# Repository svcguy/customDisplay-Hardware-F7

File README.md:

A custom display development PCB targeted to be compatible with STM32CubeMX and TouchGFX.  
Based on the STM32F767 MCU with 128Mbit external SDRAM, 512Mbit external QSPI flash.
PCB is designed to be compatible with JLCPCB's SMT service.

More to come!
Work in progress!

Changelog:
Rev A0 -    inital design.  Sent to fab
Rev B1 -    PCB changes -       move traces too close to PCB edge
                                change C23 footprint to 0805 (bom consolidation)
                                move some dimensions to B.Fab layer
            Schematic changes - change C23 footprint to 0805 (bom consolidation)
                                update some footprint properties to "virtual"
            General changes -   Generate PDF of schematic and top and bot assembly drawings

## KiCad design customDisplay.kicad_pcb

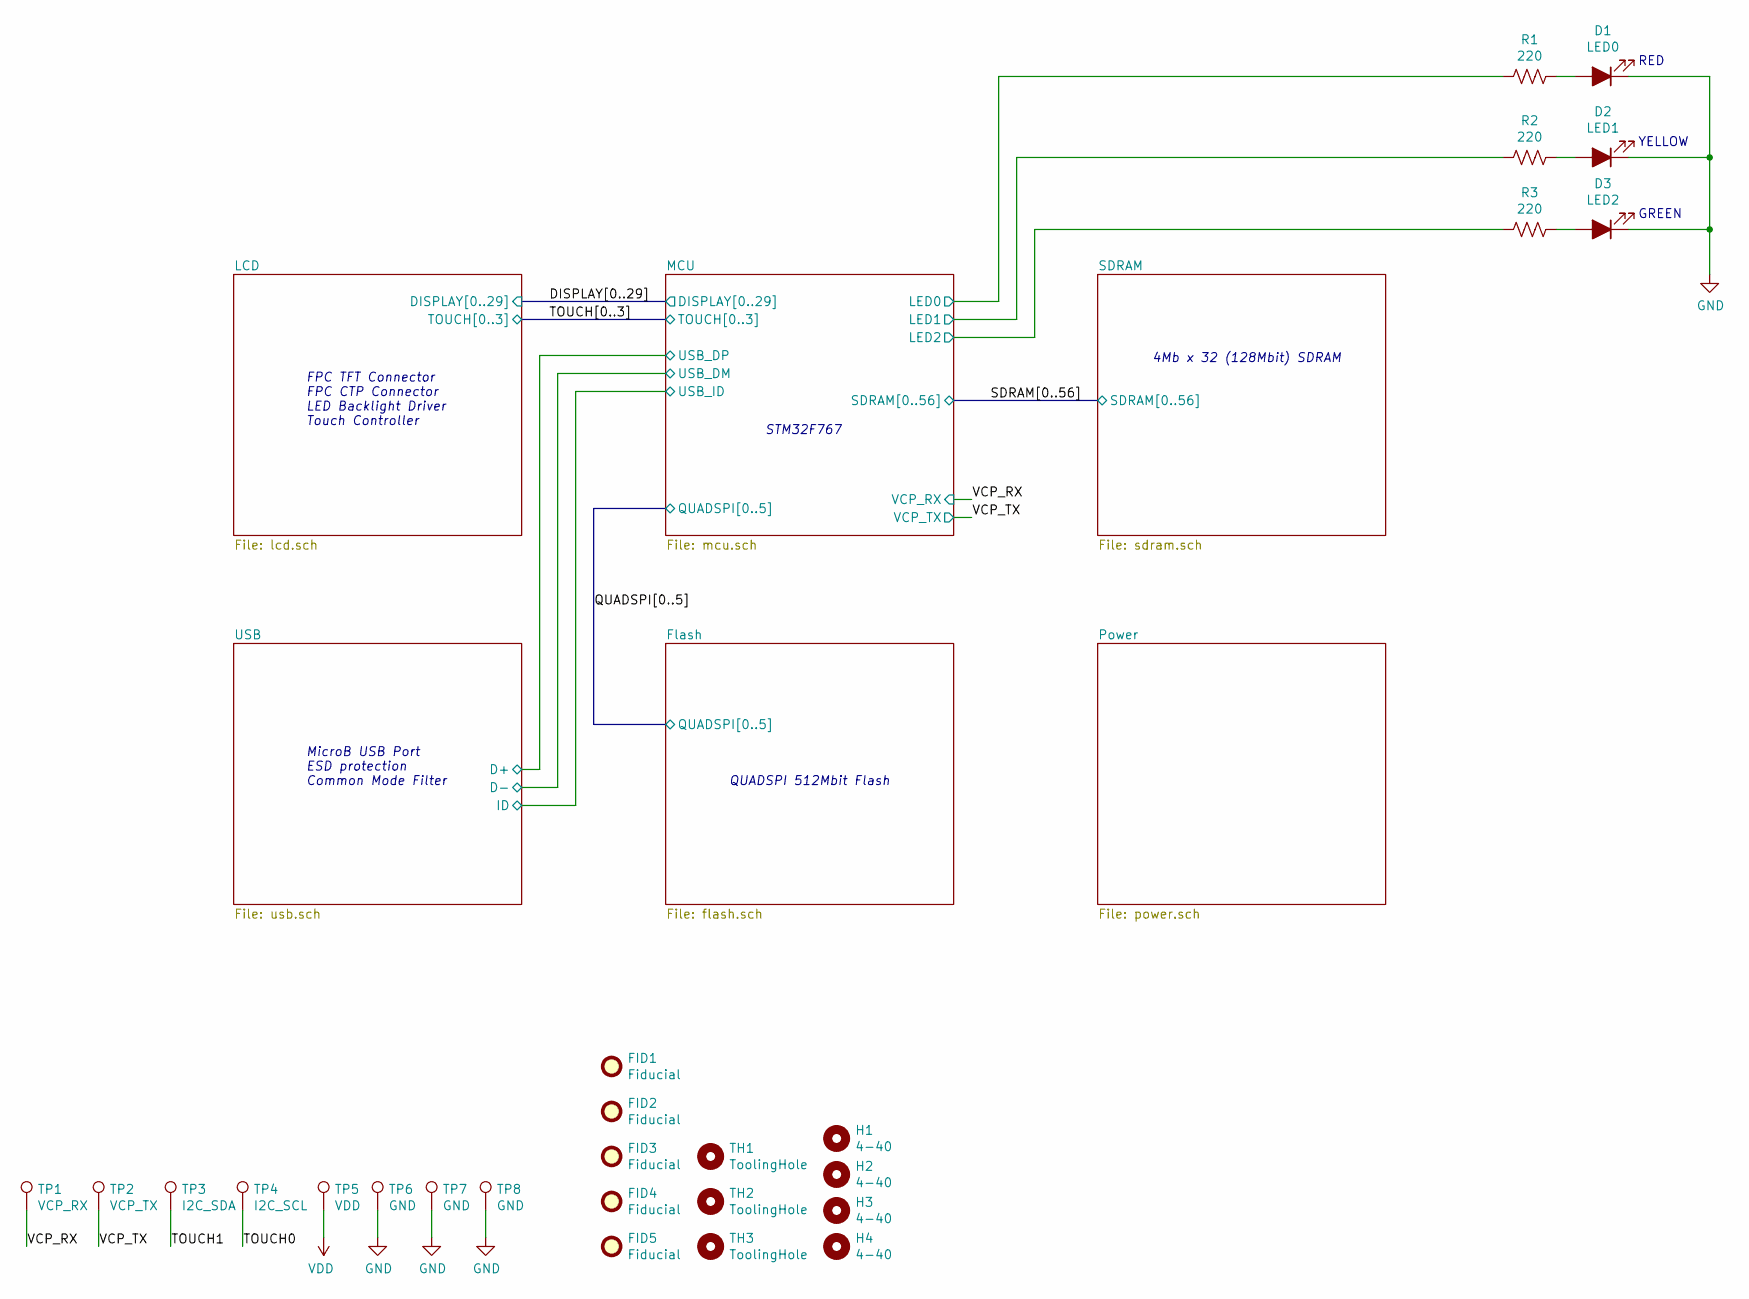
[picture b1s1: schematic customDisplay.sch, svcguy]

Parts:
D1: LED0; LED_0603_1608Metric; LCSC C2286
D2: LED1; LED_0603_1608Metric; LCSC C72038
D3: LED2; LED_0603_1608Metric; LCSC C72043
FID1, FID2, FID3, FID4, FID5: Fiducial; Fiducial_1mm_Mask2mm; Digikey DNP
H1, H2, H3, H4: 4-40; MountingHole_3.2mm_M3; LCSC DNP
R1, R2, R3: 220; R_0402_1005Metric; LCSC C25091
TH1, TH2, TH3: ToolingHole; JLC_TOOLING_HOLE; Digikey DNP
TP1: VCP_RX; TestPoint_THTPad_1.0x1.0mm_Drill0.5mm; LCSC DNP
TP2: VCP_TX; TestPoint_THTPad_1.0x1.0mm_Drill0.5mm; LCSC DNP
TP3: I2C_SDA; TestPoint_THTPad_1.0x1.0mm_Drill0.5mm; LCSC DNP
TP4: I2C_SCL; TestPoint_THTPad_1.0x1.0mm_Drill0.5mm; LCSC DNP
TP5: VDD; TestPoint_THTPad_1.0x1.0mm_Drill0.5mm; LCSC DNP
TP6, TP7: GND; TestPoint_THTPad_1.0x1.0mm_Drill0.5mm; LCSC DNP
TP8: GND; H9001-01; LCSC DNP

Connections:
/MCU/LED0: R1.2; also elsewhere on the board
/MCU/LED1: R2.2; also elsewhere on the board
/MCU/LED2: R3.2; also elsewhere on the board
/TOUCH0: TP4.1; also elsewhere on the board
/TOUCH1: TP3.1; also elsewhere on the board
/VCP_RX: TP1.1; also elsewhere on the board
/VCP_TX: TP2.1; also elsewhere on the board
GND: D1.1 (K), D2.1 (K), D3.1 (K), TP6.1, TP7.1, TP8.1; also elsewhere on the board
unnamed: D1.2 (A), R1.1
unnamed: D2.2 (A), R2.1
unnamed: D3.2 (A), R3.1
VDD: TP5.1; also elsewhere on the board

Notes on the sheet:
RED
YELLOW
GREEN
FPC TFT Connector FPC CTP Connector LED Backlight Driver Touch Controller
MicroB USB Port ESD protection Common Mode Filter
QUADSPI 512Mbit Flash
4Mb x 32 (128Mbit) SDRAM
STM32F767

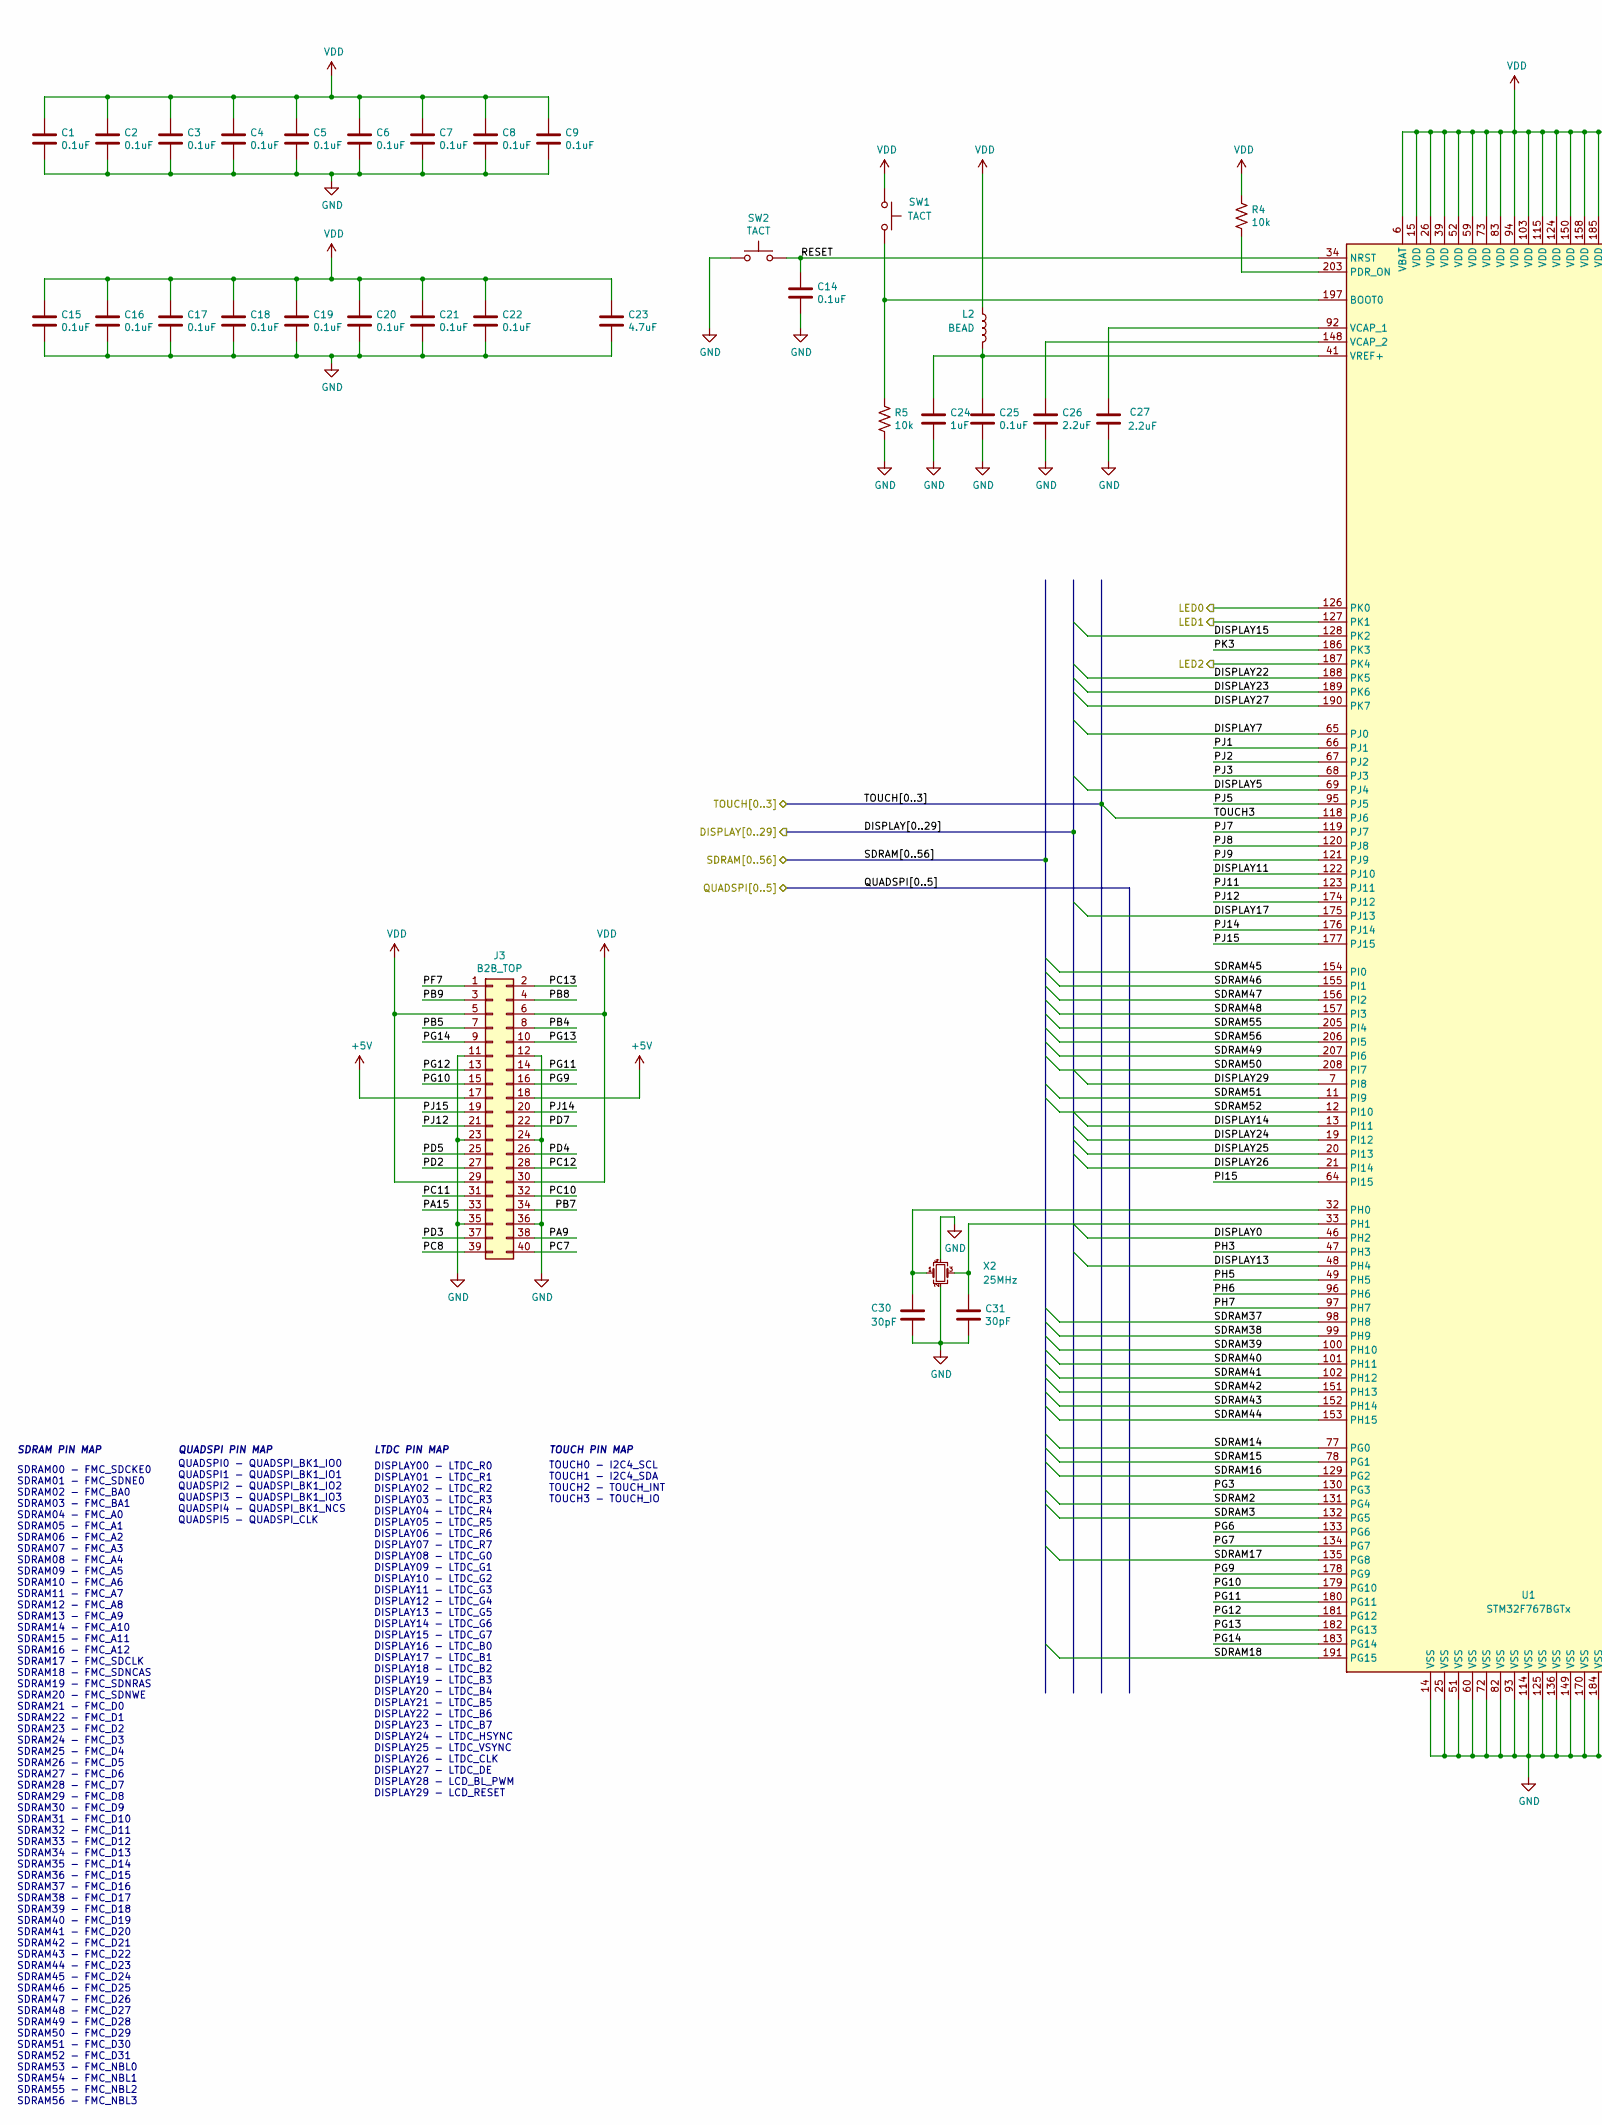
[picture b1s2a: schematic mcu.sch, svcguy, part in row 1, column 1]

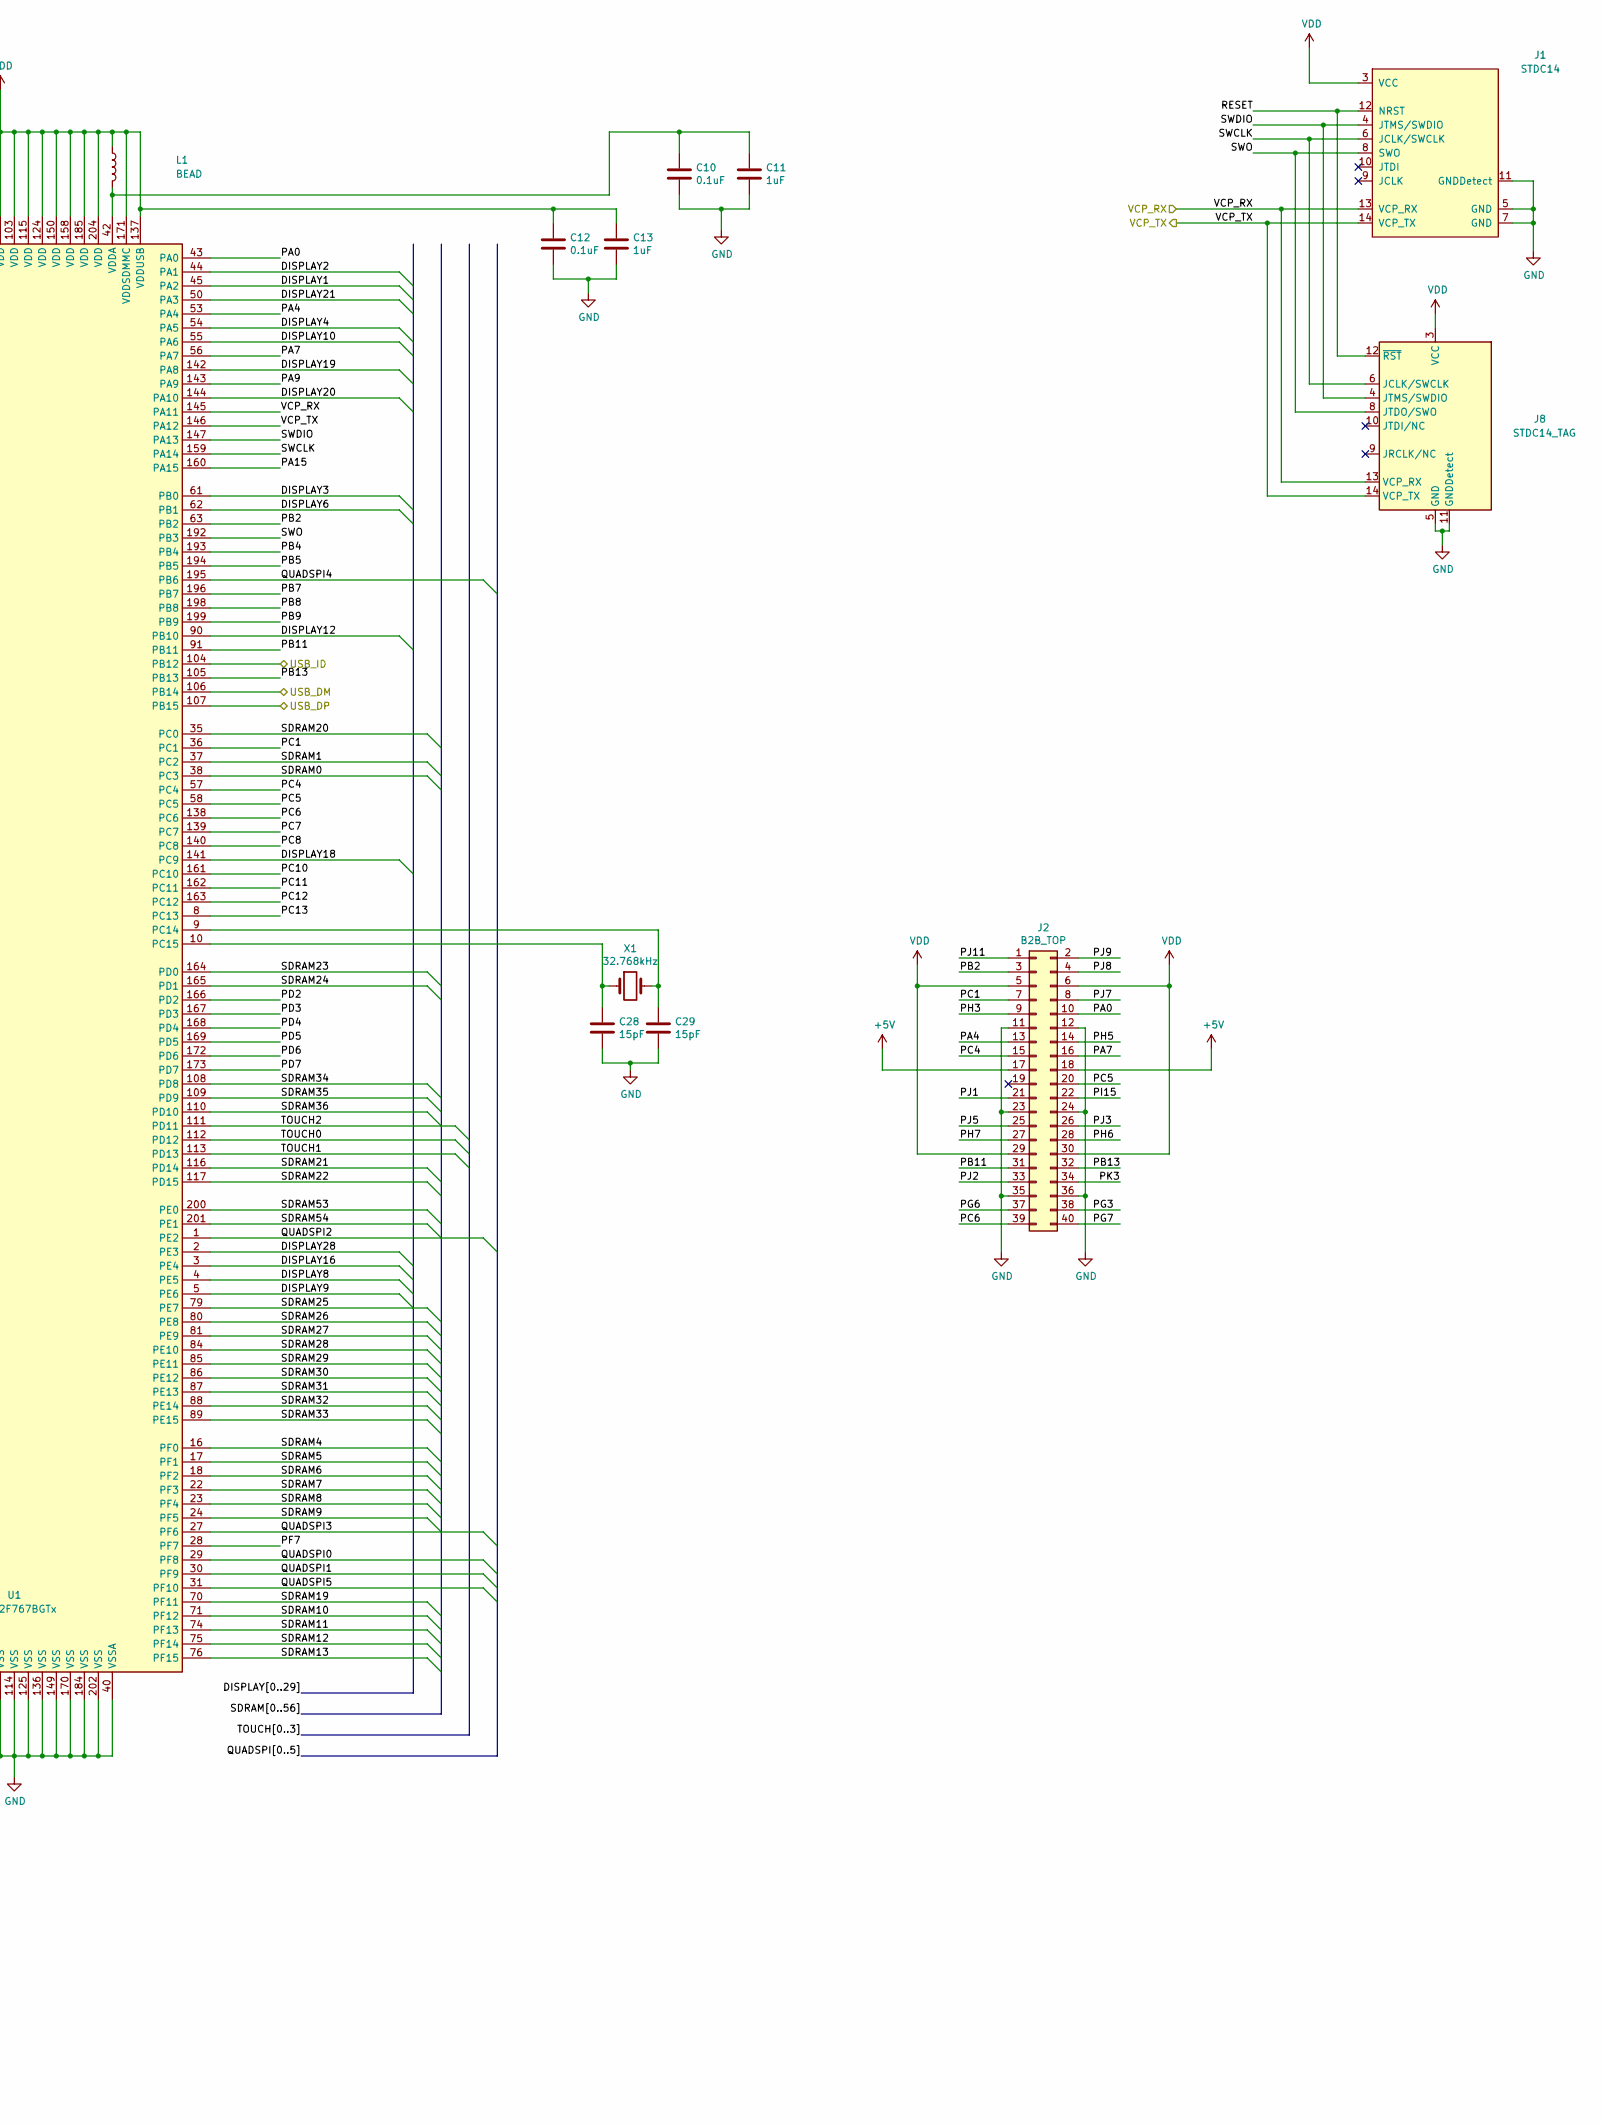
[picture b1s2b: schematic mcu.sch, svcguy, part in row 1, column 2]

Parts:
C1, C2, C3, C4, C5, C6, C7, C8, C9, C10, C12, C14, C15, C16, C17, C18, C19, C20, C21, C22, C25: 0.1uF; C_0402_1005Metric; LCSC C1525
C11, C13, C24: 1uF; C_0402_1005Metric; LCSC C52923
C23: 4.7uF; C_0805_2012Metric; LCSC C19666
C26, C27: 2.2uF; C_0603_1608Metric; LCSC C23630
C28, C29: 15pF; C_0402_1005Metric; LCSC C1548
C30, C31: 30pF; C_0402_1005Metric; LCSC C1570
J1: STDC14; STDC14_BOX; LCSC DNP
J2, J3: B2B_TOP; FX6A-040P-0.8SV; LCSC DNP
J8: STDC14_TAG; Tag-Connect_TC2070-IDC-FP_2x07_P1.27mm_Vertical; LCSC DNP
L1, L2: BEAD; L_0805_2012Metric; LCSC C1015
R4, R5: 10k; R_0402_1005Metric; LCSC C25744
SW1, SW2: TACT; TS_1187A; LCSC C318889
U1: STM32F767BGTx; LQFP-208_28x28mm_P0.5mm; LCSC C129277
X1: 32.768kHz; Crystal_SMD_3215-2Pin_3.2x1.5mm; LCSC C32346
X2: 25MHz; Crystal_SMD_3225-4Pin_3.2x2.5mm; LCSC C9006

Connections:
+5V: J2.17, J2.18, J3.17, J3.18; also elsewhere on the board
/Flash/QUADSPI0: U1.29 (PF8); also elsewhere on the board
/Flash/QUADSPI1: U1.30 (PF9); also elsewhere on the board
/Flash/QUADSPI2: U1.1 (PE2); also elsewhere on the board
/Flash/QUADSPI3: U1.27 (PF6); also elsewhere on the board
/Flash/QUADSPI4: U1.195 (PB6); also elsewhere on the board
/Flash/QUADSPI5: U1.31 (PF10); also elsewhere on the board
/LCD/DISPLAY0: U1.46 (PH2); also elsewhere on the board
/LCD/DISPLAY1: U1.45 (PA2); also elsewhere on the board
/LCD/DISPLAY2: U1.44 (PA1); also elsewhere on the board
/LCD/DISPLAY3: U1.61 (PB0); also elsewhere on the board
/LCD/DISPLAY4: U1.54 (PA5); also elsewhere on the board
/LCD/DISPLAY5: U1.69 (PJ4); also elsewhere on the board
/LCD/DISPLAY6: U1.62 (PB1); also elsewhere on the board
/LCD/DISPLAY7: U1.65 (PJ0); also elsewhere on the board
/LCD/DISPLAY8: U1.4 (PE5); also elsewhere on the board
/LCD/DISPLAY9: U1.5 (PE6); also elsewhere on the board
/LCD/DISPLAY10: U1.55 (PA6); also elsewhere on the board
/LCD/DISPLAY11: U1.122 (PJ10); also elsewhere on the board
/LCD/DISPLAY12: U1.90 (PB10); also elsewhere on the board
/LCD/DISPLAY13: U1.48 (PH4); also elsewhere on the board
/LCD/DISPLAY14: U1.13 (PI11); also elsewhere on the board
/LCD/DISPLAY15: U1.128 (PK2); also elsewhere on the board
/LCD/DISPLAY16: U1.3 (PE4); also elsewhere on the board
/LCD/DISPLAY17: U1.175 (PJ13); also elsewhere on the board
/LCD/DISPLAY18: U1.141 (PC9); also elsewhere on the board
/LCD/DISPLAY19: U1.142 (PA8); also elsewhere on the board
/LCD/DISPLAY20: U1.144 (PA10); also elsewhere on the board
/LCD/DISPLAY21: U1.50 (PA3); also elsewhere on the board
/LCD/DISPLAY22: U1.188 (PK5); also elsewhere on the board
/LCD/DISPLAY23: U1.189 (PK6); also elsewhere on the board
/LCD/DISPLAY24: U1.19 (PI12); also elsewhere on the board
/LCD/DISPLAY25: U1.20 (PI13); also elsewhere on the board
/LCD/DISPLAY26: U1.21 (PI14); also elsewhere on the board
/LCD/DISPLAY27: U1.190 (PK7); also elsewhere on the board
/LCD/DISPLAY28: U1.2 (PE3); also elsewhere on the board
/LCD/DISPLAY29: U1.7 (PI8); also elsewhere on the board
/LCD/TOUCH2: U1.111 (PD11); also elsewhere on the board
/LCD/TOUCH3: U1.118 (PJ6); also elsewhere on the board
/MCU/LED0: U1.126 (PK0); also elsewhere on the board
/MCU/LED1: U1.127 (PK1); also elsewhere on the board
/MCU/LED2: U1.187 (PK4); also elsewhere on the board
/MCU/PA0: J2.10, U1.43 (PA0)
/MCU/PA4: J2.13, U1.53 (PA4)
/MCU/PA7: J2.16, U1.56 (PA7)
/MCU/PA9: J3.38, U1.143 (PA9)
/MCU/PA15: J3.33, U1.160 (PA15)
/MCU/PB2: J2.3, U1.63 (PB2)
/MCU/PB4: J3.8, U1.193 (PB4)
/MCU/PB5: J3.7, U1.194 (PB5)
/MCU/PB7: J3.34, U1.196 (PB7)
/MCU/PB8: J3.4, U1.198 (PB8)
/MCU/PB9: J3.3, U1.199 (PB9)
/MCU/PB11: J2.31, U1.91 (PB11)
/MCU/PB13: J2.32, U1.105 (PB13)
/MCU/PC1: J2.7, U1.36 (PC1)
/MCU/PC4: J2.15, U1.57 (PC4)
/MCU/PC5: J2.20, U1.58 (PC5)
/MCU/PC6: J2.39, U1.138 (PC6)
/MCU/PC7: J3.40, U1.139 (PC7)
/MCU/PC8: J3.39, U1.140 (PC8)
/MCU/PC10: J3.32, U1.161 (PC10)
/MCU/PC11: J3.31, U1.162 (PC11)
/MCU/PC12: J3.28, U1.163 (PC12)
/MCU/PC13: J3.2, U1.8 (PC13)
/MCU/PD2: J3.27, U1.166 (PD2)
/MCU/PD3: J3.37, U1.167 (PD3)
/MCU/PD4: J3.26, U1.168 (PD4)
/MCU/PD5: J3.25, U1.169 (PD5)
/MCU/PD7: J3.22, U1.173 (PD7)
/MCU/PF7: J3.1, U1.28 (PF7)
/MCU/PG3: J2.38, U1.130 (PG3)
/MCU/PG6: J2.37, U1.133 (PG6)
/MCU/PG7: J2.40, U1.134 (PG7)
/MCU/PG9: J3.16, U1.178 (PG9)
/MCU/PG10: J3.15, U1.179 (PG10)
/MCU/PG11: J3.14, U1.180 (PG11)
/MCU/PG12: J3.13, U1.181 (PG12)
/MCU/PG13: J3.10, U1.182 (PG13)
/MCU/PG14: J3.9, U1.183 (PG14)
/MCU/PH3: J2.9, U1.47 (PH3)
/MCU/PH5: J2.14, U1.49 (PH5)
/MCU/PH6: J2.28, U1.96 (PH6)
/MCU/PH7: J2.27, U1.97 (PH7)
/MCU/PI15: J2.22, U1.64 (PI15)
/MCU/PJ1: J2.21, U1.66 (PJ1)
/MCU/PJ2: J2.33, U1.67 (PJ2)
/MCU/PJ3: J2.26, U1.68 (PJ3)
/MCU/PJ5: J2.25, U1.95 (PJ5)
/MCU/PJ7: J2.8, U1.119 (PJ7)
/MCU/PJ8: J2.4, U1.120 (PJ8)
/MCU/PJ9: J2.2, U1.121 (PJ9)
/MCU/PJ11: J2.1, U1.123 (PJ11)
/MCU/PJ12: J3.21, U1.174 (PJ12)
/MCU/PJ14: J3.20, U1.176 (PJ14)
/MCU/PJ15: J3.19, U1.177 (PJ15)
/MCU/PK3: J2.34, U1.186 (PK3)
/MCU/RESET: C14.1, J1.12 (NRST), J8.12 (~RST), SW2.2, U1.34 (NRST)
/MCU/SDRAM0: U1.38 (PC3); also elsewhere on the board
/MCU/SDRAM1: U1.37 (PC2); also elsewhere on the board
/MCU/SDRAM2: U1.131 (PG4); also elsewhere on the board
/MCU/SDRAM3: U1.132 (PG5); also elsewhere on the board
/MCU/SDRAM4: U1.16 (PF0); also elsewhere on the board
/MCU/SDRAM5: U1.17 (PF1); also elsewhere on the board
/MCU/SDRAM6: U1.18 (PF2); also elsewhere on the board
/MCU/SDRAM7: U1.22 (PF3); also elsewhere on the board
/MCU/SDRAM8: U1.23 (PF4); also elsewhere on the board
/MCU/SDRAM9: U1.24 (PF5); also elsewhere on the board
/MCU/SDRAM10: U1.71 (PF12); also elsewhere on the board
/MCU/SDRAM11: U1.74 (PF13); also elsewhere on the board
/MCU/SDRAM12: U1.75 (PF14); also elsewhere on the board
/MCU/SDRAM13: U1.76 (PF15); also elsewhere on the board
/MCU/SDRAM14: U1.77 (PG0); also elsewhere on the board
/MCU/SDRAM15: U1.78 (PG1); also elsewhere on the board
/MCU/SDRAM16: U1.129 (PG2); also elsewhere on the board
/MCU/SDRAM17: U1.135 (PG8); also elsewhere on the board
/MCU/SDRAM18: U1.191 (PG15); also elsewhere on the board
/MCU/SDRAM19: U1.70 (PF11); also elsewhere on the board
/MCU/SDRAM20: U1.35 (PC0); also elsewhere on the board
/MCU/SDRAM21: U1.116 (PD14); also elsewhere on the board
/MCU/SDRAM22: U1.117 (PD15); also elsewhere on the board
/MCU/SDRAM23: U1.164 (PD0); also elsewhere on the board
/MCU/SDRAM24: U1.165 (PD1); also elsewhere on the board
/MCU/SDRAM25: U1.79 (PE7); also elsewhere on the board
/MCU/SDRAM26: U1.80 (PE8); also elsewhere on the board
/MCU/SDRAM27: U1.81 (PE9); also elsewhere on the board
/MCU/SDRAM28: U1.84 (PE10); also elsewhere on the board
/MCU/SDRAM29: U1.85 (PE11); also elsewhere on the board
/MCU/SDRAM30: U1.86 (PE12); also elsewhere on the board
/MCU/SDRAM31: U1.87 (PE13); also elsewhere on the board
/MCU/SDRAM32: U1.88 (PE14); also elsewhere on the board
/MCU/SDRAM33: U1.89 (PE15); also elsewhere on the board
/MCU/SDRAM34: U1.108 (PD8); also elsewhere on the board
/MCU/SDRAM35: U1.109 (PD9); also elsewhere on the board
/MCU/SDRAM36: U1.110 (PD10); also elsewhere on the board
/MCU/SDRAM37: U1.98 (PH8); also elsewhere on the board
/MCU/SDRAM38: U1.99 (PH9); also elsewhere on the board
/MCU/SDRAM39: U1.100 (PH10); also elsewhere on the board
/MCU/SDRAM40: U1.101 (PH11); also elsewhere on the board
/MCU/SDRAM41: U1.102 (PH12); also elsewhere on the board
/MCU/SDRAM42: U1.151 (PH13); also elsewhere on the board
/MCU/SDRAM43: U1.152 (PH14); also elsewhere on the board
/MCU/SDRAM44: U1.153 (PH15); also elsewhere on the board
/MCU/SDRAM45: U1.154 (PI0); also elsewhere on the board
/MCU/SDRAM46: U1.155 (PI1); also elsewhere on the board
/MCU/SDRAM47: U1.156 (PI2); also elsewhere on the board
/MCU/SDRAM48: U1.157 (PI3); also elsewhere on the board
/MCU/SDRAM49: U1.207 (PI6); also elsewhere on the board
/MCU/SDRAM50: U1.208 (PI7); also elsewhere on the board
/MCU/SDRAM51: U1.11 (PI9); also elsewhere on the board
/MCU/SDRAM52: U1.12 (PI10); also elsewhere on the board
/MCU/SDRAM53: U1.200 (PE0); also elsewhere on the board
/MCU/SDRAM54: U1.201 (PE1); also elsewhere on the board
/MCU/SDRAM55: U1.205 (PI4); also elsewhere on the board
/MCU/SDRAM56: U1.206 (PI5); also elsewhere on the board
/MCU/SWCLK: J1.6 (JCLK/SWCLK), J8.6 (JCLK/SWCLK), U1.159 (PA14)
/MCU/SWDIO: J1.4 (JTMS/SWDIO), J8.4 (JTMS/SWDIO), U1.147 (PA13)
/MCU/SWO: J1.8 (SWO), J8.8 (JTDO/SWO), U1.192 (PB3)
/TOUCH0: U1.112 (PD12); also elsewhere on the board
/TOUCH1: U1.113 (PD13); also elsewhere on the board
/USB/ID: U1.104 (PB12); also elsewhere on the board
/VCP_RX: J1.13 (VCP_RX), J8.13 (VCP_RX), U1.145 (PA11); also elsewhere on the board
/VCP_TX: J1.14 (VCP_TX), J8.14 (VCP_TX), U1.146 (PA12); also elsewhere on the board
D+: U1.107 (PB15); also elsewhere on the board
D-: U1.106 (PB14); also elsewhere on the board
GND: C1.2, C2.2, C3.2, C4.2, C5.2, C6.2, C7.2, C8.2, C9.2, C10.2, C11.2, C12.2, C13.2, C14.2, C15.2, C16.2, C17.2, C18.2, C19.2, C20.2, C21.2, C22.2, C23.2, C24.2, C25.2, C26.2, C27.1, C28.2, C29.2, C30.2, C31.2, J1.5 (GND), J1.7 (GND), J1.11 (GNDDetect), J2.11, J2.12, J2.23, J2.24, J2.35, J2.36, J3.11, J3.12, J3.23, J3.24, J3.35, J3.36, J8.5 (GND), J8.7 (GND), J8.11 (GNDDetect), R5.2, SW2.1, U1.14 (VSS), U1.25 (VSS), U1.40 (VSSA), U1.51 (VSS), U1.60 (VSS), U1.72 (VSS), U1.82 (VSS), U1.93 (VSS), U1.114 (VSS), U1.125 (VSS), U1.136 (VSS), U1.149 (VSS), U1.170 (VSS), U1.184 (VSS), U1.202 (VSS), X2.2, X2.4; also elsewhere on the board
unnamed: C10.1, C11.1, L1.2, U1.42 (VDDA)
unnamed: C24.1, C25.1, L2.2, U1.41 (VREF+)
unnamed: C26.1, U1.148 (VCAP_2)
unnamed: C27.2, U1.92 (VCAP_1)
unnamed: C28.1, U1.10 (PC15), X1.1
unnamed: C29.1, U1.9 (PC14), X1.2
unnamed: C30.1, U1.32 (PH0), X2.1
unnamed: C31.1, U1.33 (PH1), X2.3
unnamed: R4.2, U1.203 (PDR_ON)
unnamed: R5.1, SW1.2, U1.197 (BOOT0)
VDD: C1.1, C2.1, C3.1, C4.1, C5.1, C6.1, C7.1, C8.1, C9.1, C12.1, C13.1, C15.1, C16.1, C17.1, C18.1, C19.1, C20.1, C21.1, C22.1, C23.1, J1.3 (VCC), J2.5, J2.6, J2.29, J2.30, J3.5, J3.6, J3.29, J3.30, J8.3 (VCC), L1.1, L2.1, R4.1, SW1.1, U1.6 (VBAT), U1.15 (VDD), U1.26 (VDD), U1.39 (VDD), U1.52 (VDD), U1.59 (VDD), U1.73 (VDD), U1.83 (VDD), U1.94 (VDD), U1.103 (VDD), U1.115 (VDD), U1.124 (VDD), U1.137 (VDDUSB), U1.150 (VDD), U1.158 (VDD), U1.171 (VDDSDMMC), U1.185 (VDD), U1.204 (VDD); also elsewhere on the board

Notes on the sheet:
SDRAM PIN MAP
SDRAM00 - FMC_SDCKE0 SDRAM01 - FMC_SDNE0 SDRAM02 - FMC_BA0 SDRAM03 - FMC_BA1 SDRAM04 - FMC_A0 SDRAM05 - FMC_A1 SDRAM06 - FMC_A2 SDRAM07 - FMC_A3 SDRAM08 - FMC_A4 SDRAM09 - FMC_A5 SDRAM10 - FMC_A6 SDRAM11 - FMC_A7 SDRAM12 - FMC_A8 SDRAM13 - FMC_A9 SDRAM14 - FMC_A10 SDRAM15 - FMC_A11 SDRAM16 - FMC_A1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
QUADSPI PIN MAP
QUADSPI0 - QUADSPI_BK1_IO0 QUADSPI1 - QUADSPI_BK1_IO1 QUADSPI2 - QUADSPI_BK1_IO2 QUADSPI3 - QUADSPI_BK1_IO3 QUADSPI4 - QUADSPI_BK1_NCS QUADSPI5 - QUADSPI_CLK
DISPLAY00 - LTDC_R0 DISPLAY01 - LTDC_R1 DISPLAY02 - LTDC_R2 DISPLAY03 - LTDC_R3 DISPLAY04 - LTDC_R4 DISPLAY05 - LTDC_R5 DISPLAY06 - LTDC_R6 DISPLAY07 - LTDC_R7 DISPLAY08 - LTDC_G0 DISPLAY09 - LTDC_G1 DISPLAY10 - LTDC_G2 DISPLAY11 - LTDC_G3 DISPLAY12 - LTDC_G4 DISPLAY13 - LTDC_G5 DISPLAY14 - LTDC_G6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
LTDC PIN MAP
TOUCH PIN MAP
TOUCH0 - I2C4_SCL TOUCH1 - I2C4_SDA TOUCH2 - TOUCH_INT TOUCH3 - TOUCH_IO

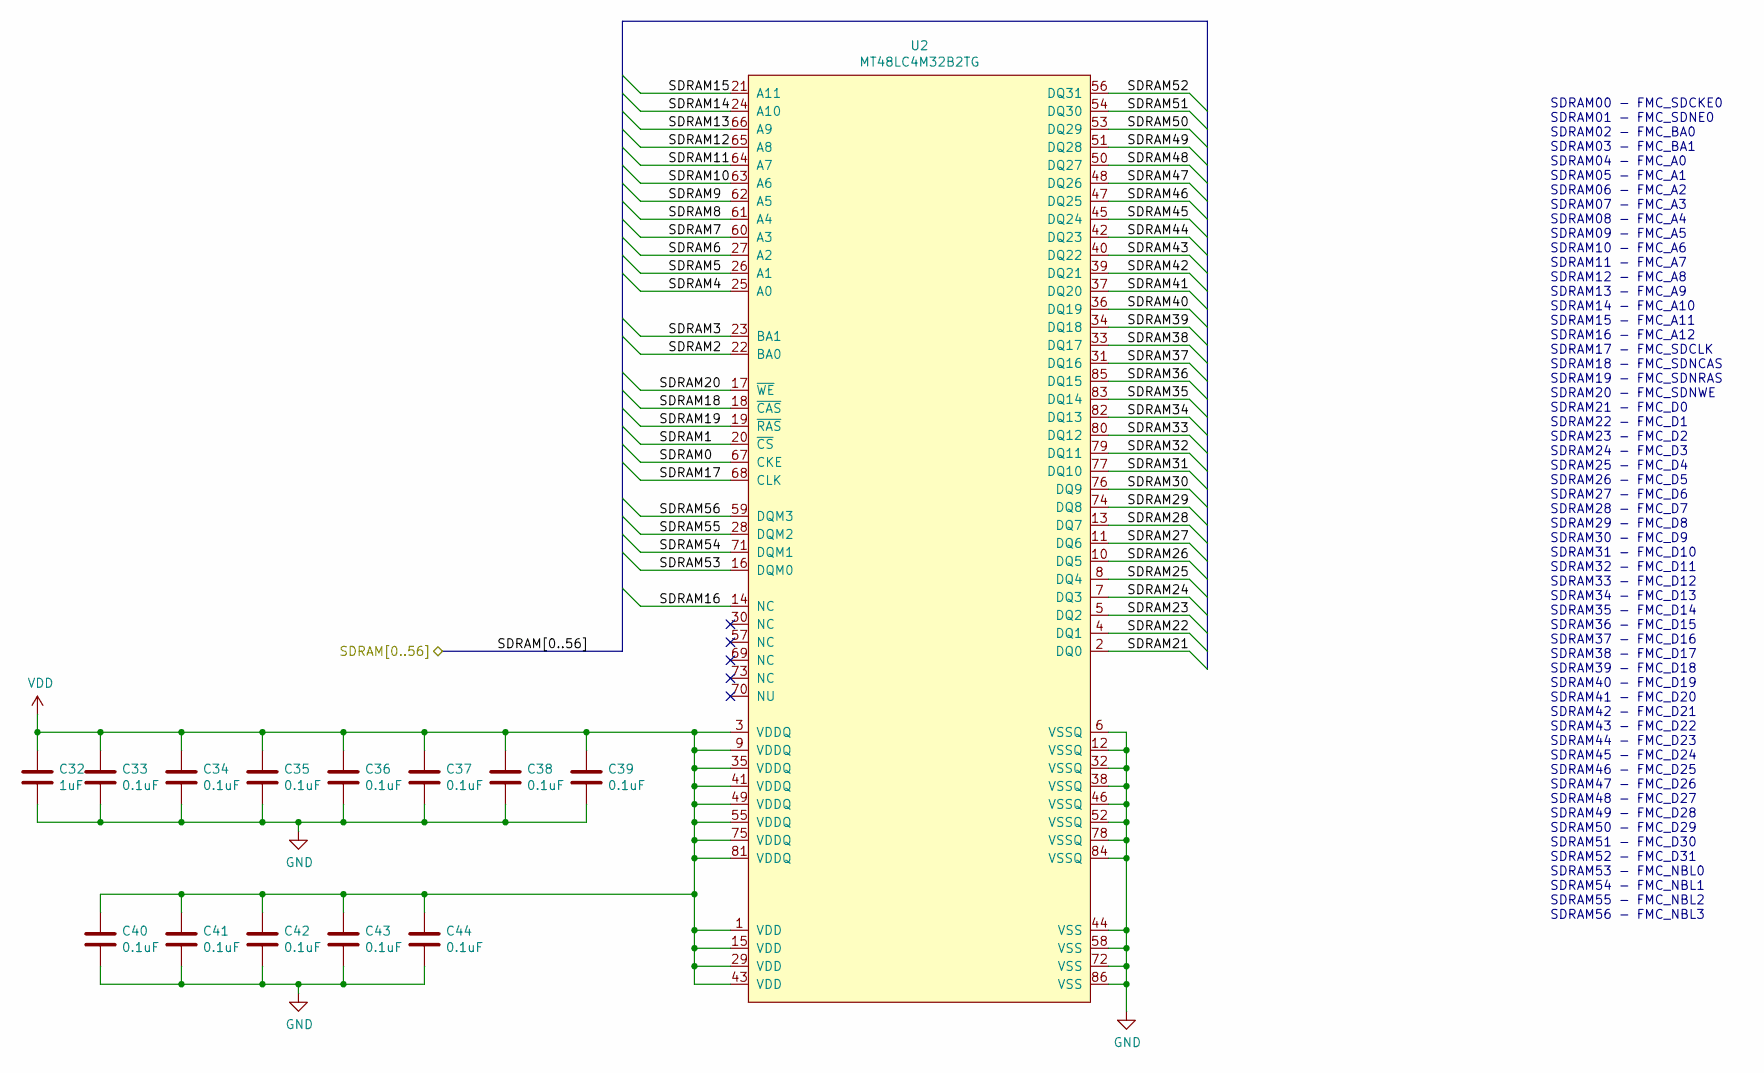
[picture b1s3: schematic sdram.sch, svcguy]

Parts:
C32: 1uF; C_0402_1005Metric; LCSC C52923
C33, C34, C35, C36, C37, C38, C39, C40, C41, C42, C43, C44: 0.1uF; C_0402_1005Metric; LCSC C1525
U2: MT48LC4M32B2TG; TSOP_II-86-400mill; LCSC C108951

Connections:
/MCU/SDRAM0: U2.67 (CKE); also elsewhere on the board
/MCU/SDRAM1: U2.20 (~CS); also elsewhere on the board
/MCU/SDRAM2: U2.22 (BA0); also elsewhere on the board
/MCU/SDRAM3: U2.23 (BA1); also elsewhere on the board
/MCU/SDRAM4: U2.25 (A0); also elsewhere on the board
/MCU/SDRAM5: U2.26 (A1); also elsewhere on the board
/MCU/SDRAM6: U2.27 (A2); also elsewhere on the board
/MCU/SDRAM7: U2.60 (A3); also elsewhere on the board
/MCU/SDRAM8: U2.61 (A4); also elsewhere on the board
/MCU/SDRAM9: U2.62 (A5); also elsewhere on the board
/MCU/SDRAM10: U2.63 (A6); also elsewhere on the board
/MCU/SDRAM11: U2.64 (A7); also elsewhere on the board
/MCU/SDRAM12: U2.65 (A8); also elsewhere on the board
/MCU/SDRAM13: U2.66 (A9); also elsewhere on the board
/MCU/SDRAM14: U2.24 (A10); also elsewhere on the board
/MCU/SDRAM15: U2.21 (A11); also elsewhere on the board
/MCU/SDRAM16: U2.14 (NC); also elsewhere on the board
/MCU/SDRAM17: U2.68 (CLK); also elsewhere on the board
/MCU/SDRAM18: U2.18 (~CAS); also elsewhere on the board
/MCU/SDRAM19: U2.19 (~RAS); also elsewhere on the board
/MCU/SDRAM20: U2.17 (~WE); also elsewhere on the board
/MCU/SDRAM21: U2.2 (DQ0); also elsewhere on the board
/MCU/SDRAM22: U2.4 (DQ1); also elsewhere on the board
/MCU/SDRAM23: U2.5 (DQ2); also elsewhere on the board
/MCU/SDRAM24: U2.7 (DQ3); also elsewhere on the board
/MCU/SDRAM25: U2.8 (DQ4); also elsewhere on the board
/MCU/SDRAM26: U2.10 (DQ5); also elsewhere on the board
/MCU/SDRAM27: U2.11 (DQ6); also elsewhere on the board
/MCU/SDRAM28: U2.13 (DQ7); also elsewhere on the board
/MCU/SDRAM29: U2.74 (DQ8); also elsewhere on the board
/MCU/SDRAM30: U2.76 (DQ9); also elsewhere on the board
/MCU/SDRAM31: U2.77 (DQ10); also elsewhere on the board
/MCU/SDRAM32: U2.79 (DQ11); also elsewhere on the board
/MCU/SDRAM33: U2.80 (DQ12); also elsewhere on the board
/MCU/SDRAM34: U2.82 (DQ13); also elsewhere on the board
/MCU/SDRAM35: U2.83 (DQ14); also elsewhere on the board
/MCU/SDRAM36: U2.85 (DQ15); also elsewhere on the board
/MCU/SDRAM37: U2.31 (DQ16); also elsewhere on the board
/MCU/SDRAM38: U2.33 (DQ17); also elsewhere on the board
/MCU/SDRAM39: U2.34 (DQ18); also elsewhere on the board
/MCU/SDRAM40: U2.36 (DQ19); also elsewhere on the board
/MCU/SDRAM41: U2.37 (DQ20); also elsewhere on the board
/MCU/SDRAM42: U2.39 (DQ21); also elsewhere on the board
/MCU/SDRAM43: U2.40 (DQ22); also elsewhere on the board
/MCU/SDRAM44: U2.42 (DQ23); also elsewhere on the board
/MCU/SDRAM45: U2.45 (DQ24); also elsewhere on the board
/MCU/SDRAM46: U2.47 (DQ25); also elsewhere on the board
/MCU/SDRAM47: U2.48 (DQ26); also elsewhere on the board
/MCU/SDRAM48: U2.50 (DQ27); also elsewhere on the board
/MCU/SDRAM49: U2.51 (DQ28); also elsewhere on the board
/MCU/SDRAM50: U2.53 (DQ29); also elsewhere on the board
/MCU/SDRAM51: U2.54 (DQ30); also elsewhere on the board
/MCU/SDRAM52: U2.56 (DQ31); also elsewhere on the board
/MCU/SDRAM53: U2.16 (DQM0); also elsewhere on the board
/MCU/SDRAM54: U2.71 (DQM1); also elsewhere on the board
/MCU/SDRAM55: U2.28 (DQM2); also elsewhere on the board
/MCU/SDRAM56: U2.59 (DQM3); also elsewhere on the board
GND: C32.2, C33.2, C34.2, C35.2, C36.2, C37.2, C38.2, C39.2, C40.2, C41.2, C42.2, C43.2, C44.2, U2.6 (VSSQ), U2.12 (VSSQ), U2.32 (VSSQ), U2.38 (VSSQ), U2.44 (VSS), U2.46 (VSSQ), U2.52 (VSSQ), U2.58 (VSS), U2.72 (VSS), U2.78 (VSSQ), U2.84 (VSSQ), U2.86 (VSS); also elsewhere on the board
VDD: C32.1, C33.1, C34.1, C35.1, C36.1, C37.1, C38.1, C39.1, C40.1, C41.1, C42.1, C43.1, C44.1, U2.1 (VDD), U2.3 (VDDQ), U2.9 (VDDQ), U2.15 (VDD), U2.29 (VDD), U2.35 (VDDQ), U2.41 (VDDQ), U2.43 (VDD), U2.49 (VDDQ), U2.55 (VDDQ), U2.75 (VDDQ), U2.81 (VDDQ); also elsewhere on the board

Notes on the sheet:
SDRAM00 - FMC_SDCKE0 SDRAM01 - FMC_SDNE0 SDRAM02 - FMC_BA0 SDRAM03 - FMC_BA1 SDRAM04 - FMC_A0 SDRAM05 - FMC_A1 SDRAM06 - FMC_A2 SDRAM07 - FMC_A3 SDRAM08 - FMC_A4 SDRAM09 - FMC_A5 SDRAM10 - FMC_A6 SDRAM11 - FMC_A7 SDRAM12 - FMC_A8 SDRAM13 - FMC_A9 SDRAM14 - FMC_A10 SDRAM15 - FMC_A11 SDRAM16 - FMC_A1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
